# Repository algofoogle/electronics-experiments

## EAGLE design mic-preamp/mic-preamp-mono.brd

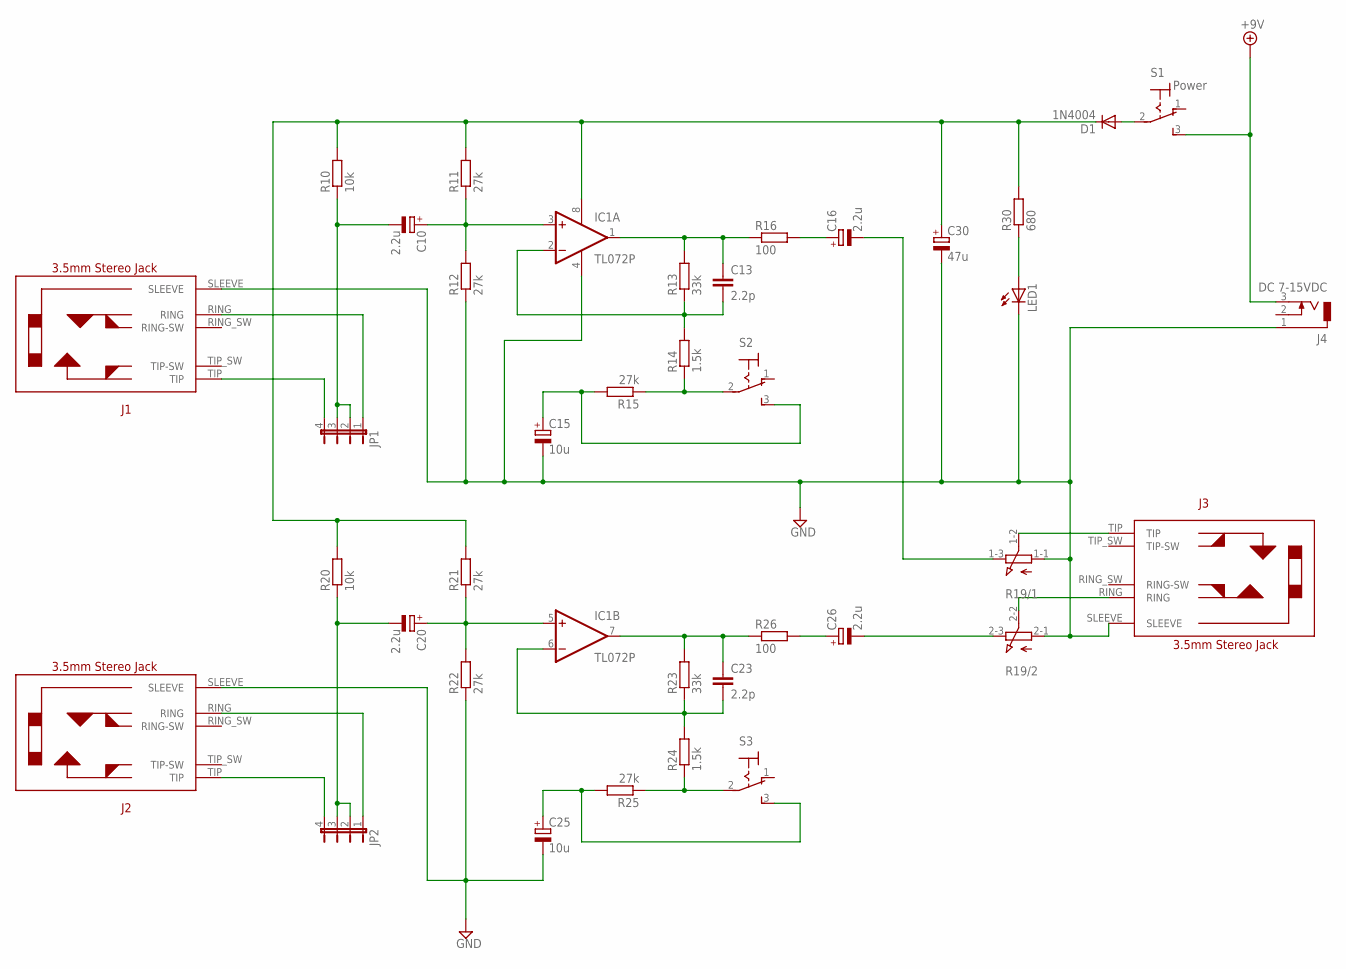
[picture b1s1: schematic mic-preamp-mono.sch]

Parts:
C10, C16, C20, C26: 2.2u; E2-5
C13, C23: 2.2p; C025-024X044
C15, C25: 10u; E2-5
C30: 47u; E2-5
D1: 1N4004; DO41-10
IC1: TL072P; DIL08
J1, J2: PICAXE_STEREOJACKSOCKET
J3: Stereo Out; PICAXE_STEREOJACKSOCKET
J4: DC 7-15VDC; DCJ0202
JP1, JP2: JP4E; JP4
LED1: LED5MM
R10, R20: 10k; 0207/5V
R11, R12, R15, R21, R22, R25: 27k; 0207/5V
R13, R23: 33k; 0207/5V
R14, R24: 1.5k; 0207/5V
R16, R26: 100; 0207/5V
R19: 3RP/1610G
R30: 680; 0207/12
S1: Power; M9040P
S2, S3: M9040P

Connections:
+9V: J4.3, S1.3 (S)
GND: C15.-, C25.-, C30.-, IC1.4 (V-), J1.SLEEVE, J2.SLEEVE, J3.SLEEVE, J4.1, LED1.K (C), R12.1, R19.1-1 (A), R19.2-1 (A), R22.1
unnamed: C10.+, IC1.3 (+IN), R11.1, R12.2
unnamed: C13.1, IC1.1 (OUT), R13.2, R16.1
unnamed: C13.2, IC1.2 (-IN), R13.1, R14.2
unnamed: C30.+, D1.C, IC1.8 (V+), R10.2, R11.2, R20.2, R21.2, R30.2
unnamed: R14.1, R15.1, S2.2
unnamed: C16.+, R16.2
unnamed: C10.-, JP1.2, JP1.3, R10.1
unnamed: D1.A, S1.2
unnamed: C15.+, R15.2, S2.3 (S)
unnamed: C16.-, R19.1-3 (E)
unnamed: LED1.A, R30.1
unnamed: C20.+, IC1.5 (+IN), R21.1, R22.2
unnamed: C26.-, R19.2-3 (E)
unnamed: J1.TIP, JP1.4
unnamed: J1.RING, JP1.1
unnamed: C23.1, IC1.7 (OUT), R23.2, R26.1
unnamed: C23.2, IC1.6 (-IN), R23.1, R24.2
unnamed: J3.RING, R19.2-2 (S)
unnamed: R24.1, R25.1, S3.2
unnamed: C26.+, R26.2
unnamed: C20.-, JP2.2, JP2.3, R20.1
unnamed: C25.+, R25.2, S3.3 (S)
unnamed: J3.TIP, R19.1-2 (S)
unnamed: J2.TIP, JP2.4
unnamed: J2.RING, JP2.1

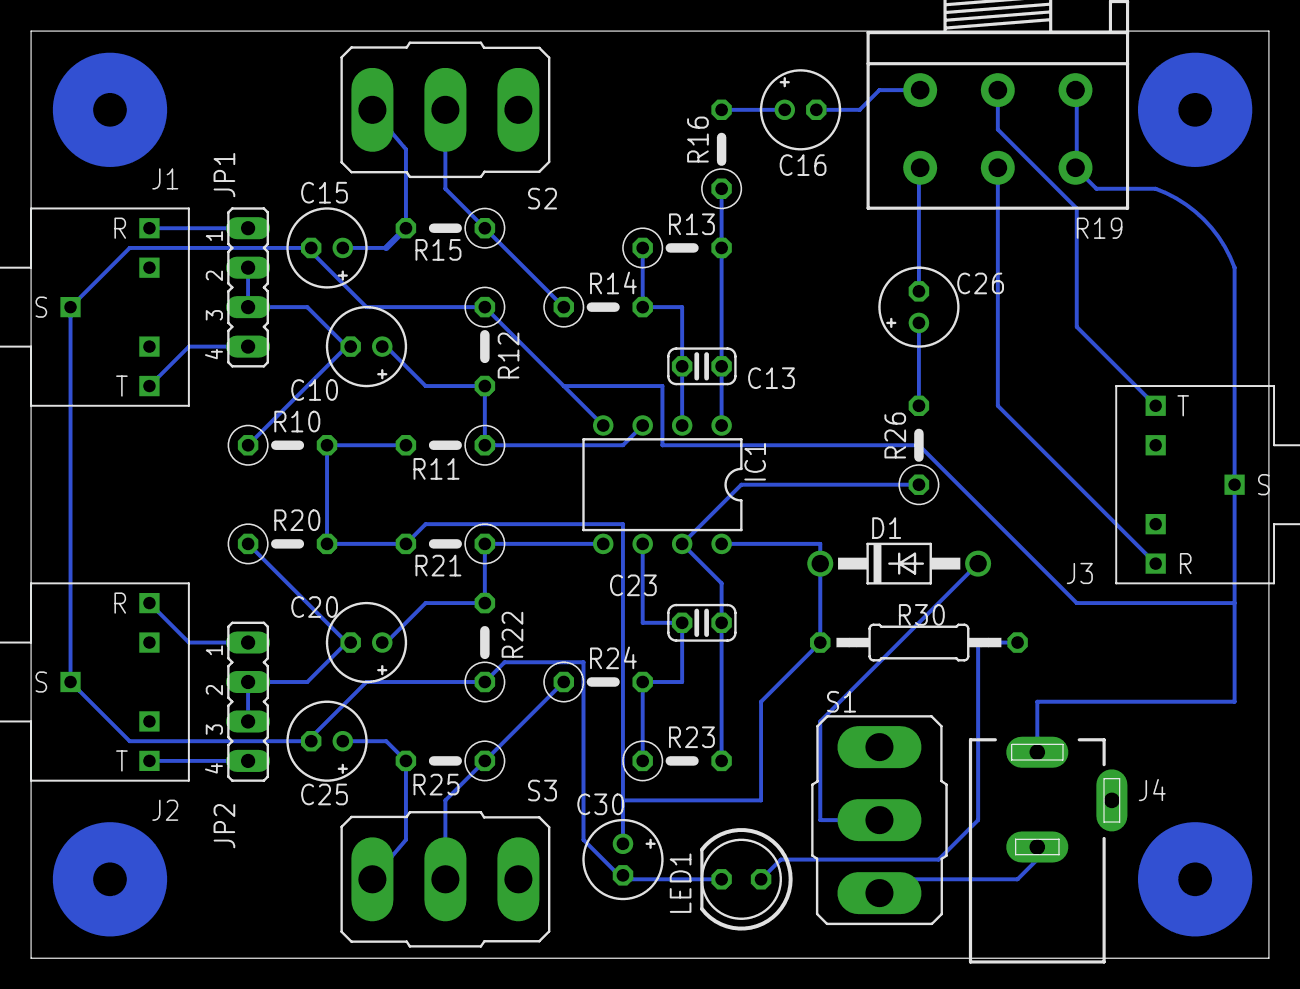
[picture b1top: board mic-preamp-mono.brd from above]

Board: 1 copper layer, 79.7 x 59.7 mm, 37 parts (0 on the bottom side), 27 nets.

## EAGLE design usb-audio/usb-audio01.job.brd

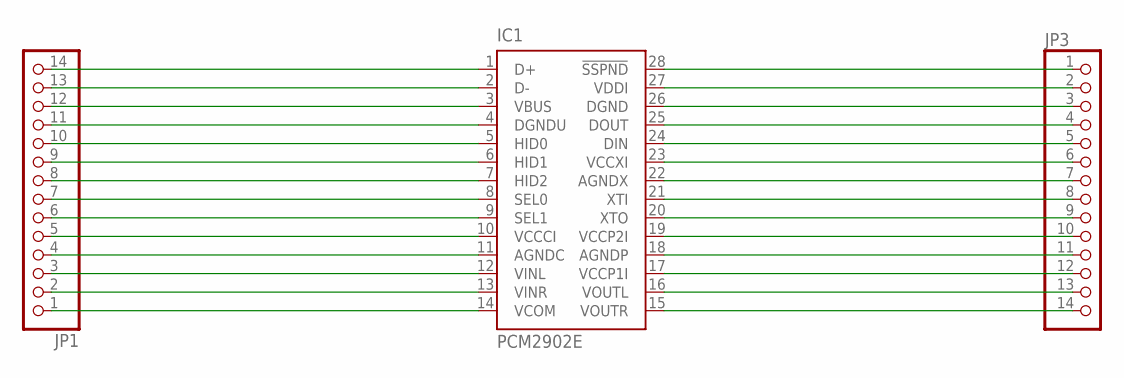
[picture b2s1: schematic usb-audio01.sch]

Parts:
IC1: PCM2902E; SSOP28DB
JP1, JP3: PINHD-1X14; 1X14

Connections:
unnamed: IC1.28 (!SSPND), JP3.1
unnamed: IC1.27 (VDDI), JP3.2
unnamed: IC1.26 (DGND), JP3.3
unnamed: IC1.25 (DOUT), JP3.4
unnamed: IC1.24 (DIN), JP3.5
unnamed: IC1.23 (VCCXI), JP3.6
unnamed: IC1.22 (AGNDX), JP3.7
unnamed: IC1.21 (XTI), JP3.8
unnamed: IC1.20 (XTO), JP3.9
unnamed: IC1.19 (VCCP2I), JP3.10
unnamed: IC1.18 (AGNDP), JP3.11
unnamed: IC1.17 (VCCP1I), JP3.12
unnamed: IC1.16 (VOUTL), JP3.13
unnamed: IC1.15 (VOUTR), JP3.14
unnamed: IC1.14 (VCOM), JP1.1
unnamed: IC1.13 (VINR), JP1.2
unnamed: IC1.12 (VINL), JP1.3
unnamed: IC1.11 (AGNDC), JP1.4
unnamed: IC1.10 (VCCCI), JP1.5
unnamed: IC1.9 (SEL1), JP1.6
unnamed: IC1.8 (SEL0), JP1.7
unnamed: IC1.7 (HID2), JP1.8
unnamed: IC1.6 (HID1), JP1.9
unnamed: IC1.5 (HID0), JP1.10
unnamed: IC1.4 (DGNDU), JP1.11
unnamed: IC1.3 (VBUS), JP1.12
unnamed: IC1.2 (D-), JP1.13
unnamed: IC1.1 (D+), JP1.14

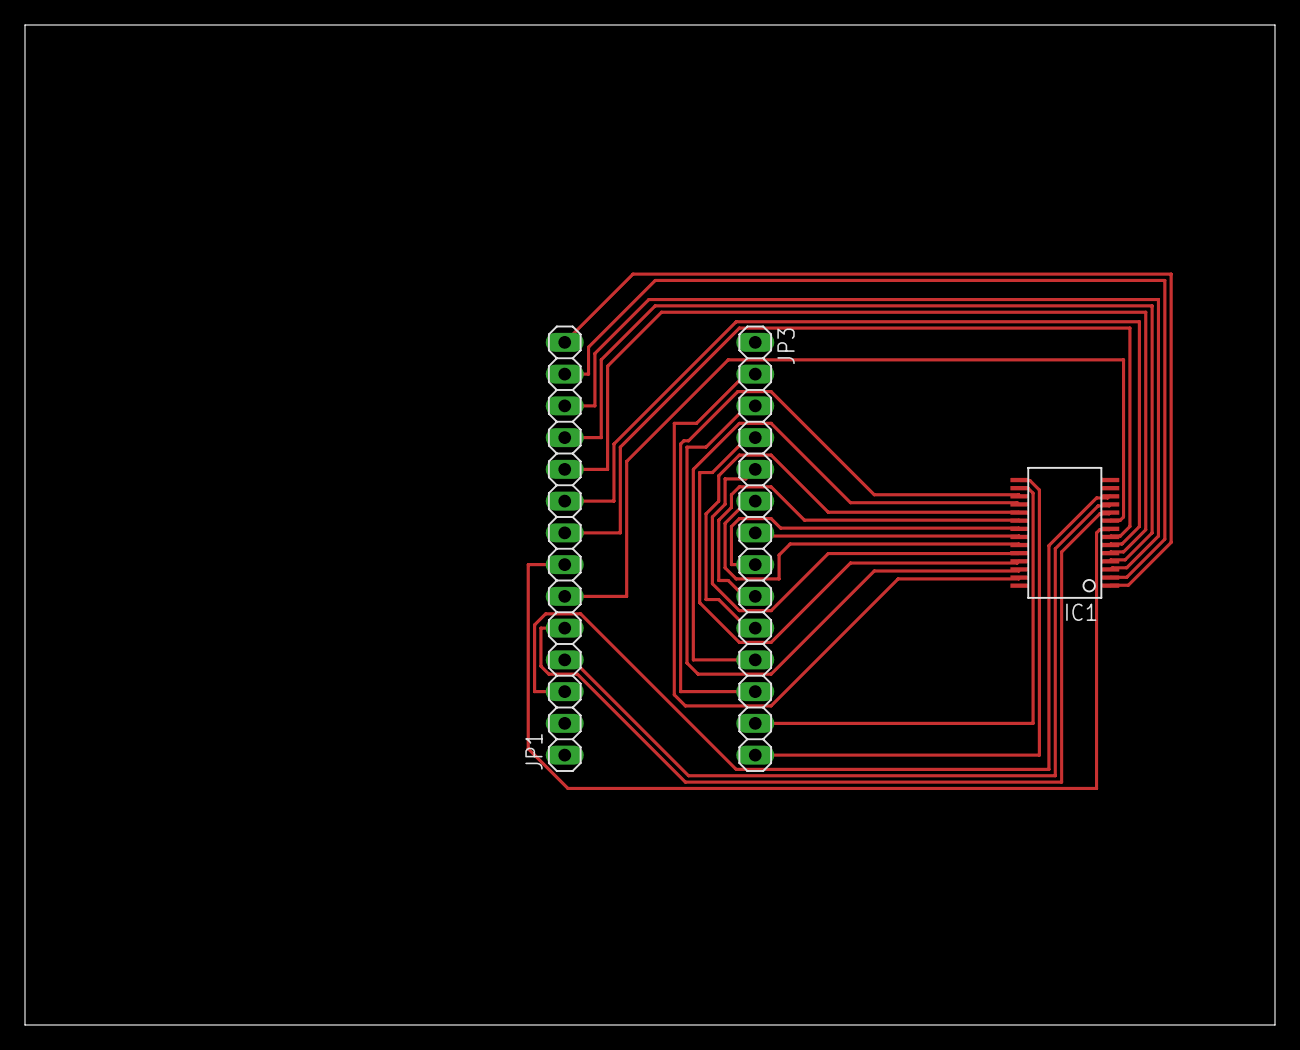
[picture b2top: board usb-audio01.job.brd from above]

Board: 1 copper layer, 100.0 x 80.0 mm, 3 parts (0 on the bottom side), 28 nets.

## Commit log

2012-11-28 Added my first library, and continuing SSM2166 schematics
2012-12-02 Continuing SSM2166 board schematics
2012-12-02 Continuing SSM2166 board schematics...
2012-12-04 Still going on SSM2166 schematics. Just need output and then can clone to Right side?
2012-12-04 Some corrections to SSM2166 schematic, and filling in more missing stuff
2012-12-17 Added 4-pin header to anton.lbr
2012-12-17 Added voltage regulator and USB passthru to SSM2166 board schematics
